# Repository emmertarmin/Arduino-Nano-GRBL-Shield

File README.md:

# Arduino-Nano-GRBL-Shield
This CNC Shield was designed to replace a "Stepper Bricklet" from Tinkerforge. It is much larger in size, but the four screw holes are compatible in size and placement.

## Features
- 102mm x 50mm
- Arduino Nano pinout is designed for GRBL firmware.
- 3 individual "X-Y-Z" stepper drivers, with a fourth "A" Axis whose `step` and `dir` pins can be coupled with either of the other three axes.
- Limit switches per axis are connected in series for NC switch operation. This means the Arduino is going to expect a closed circuit on all 6 switches (if switches are enabled in the firmware) and interpret an open circuit as a triggered switch.
- Switches have RC circuits as is [recommended by GRBL](https://github.com/gnea/grbl/wiki/Wiring-Limit-Switches) for noise filtering. These SMD parts can be left unpopulated.
- 12V Barrel Jack power source for stepper motors.
- If Arduino is to be driven without an active USB connection, the 12V source is to be stepped down to 6-7 Volts with a switching regulator. I used [this DSN-1504 one](https://www.hestore.hu/prod_10038118.html?lang=en) from Hestore.
- The only smd parts that are needed for operation are one 10k pullup resistor on the `EN` pin under the Arduino, and 12 pieces of 100k pulldown resistors right next to the stepper drivers, which control `MS1-MS3` pins to set microstepping.

> Please make sure your Arduino Nano can handle an external 6-7V source on VIN and an active USB connection simultaneously. Officially it should be able to do that, but there's stories on the internet about versions of Nanos that got burnt.

> Also, while a direct 12V source on the VIN of the Arduino is officially fine, it's not recommended, as the internal regulator of the Arduino will dissipate the 7V difference in form of heat. This is why I used a switching step-down converter.

## Images

Renders were created with [tracespace.io](https://tracespace.io/)

The images below show an earlier version which lacked the RC filters. Apart from that it's the same. Please excuse the dusty Nano.

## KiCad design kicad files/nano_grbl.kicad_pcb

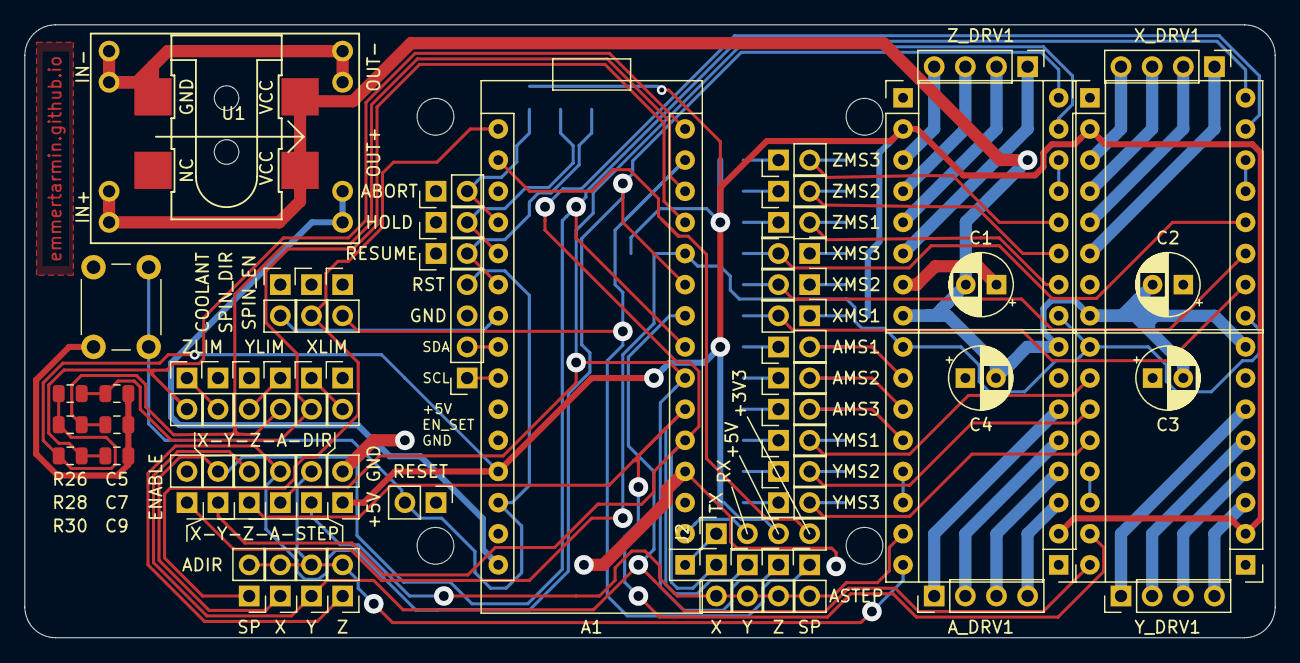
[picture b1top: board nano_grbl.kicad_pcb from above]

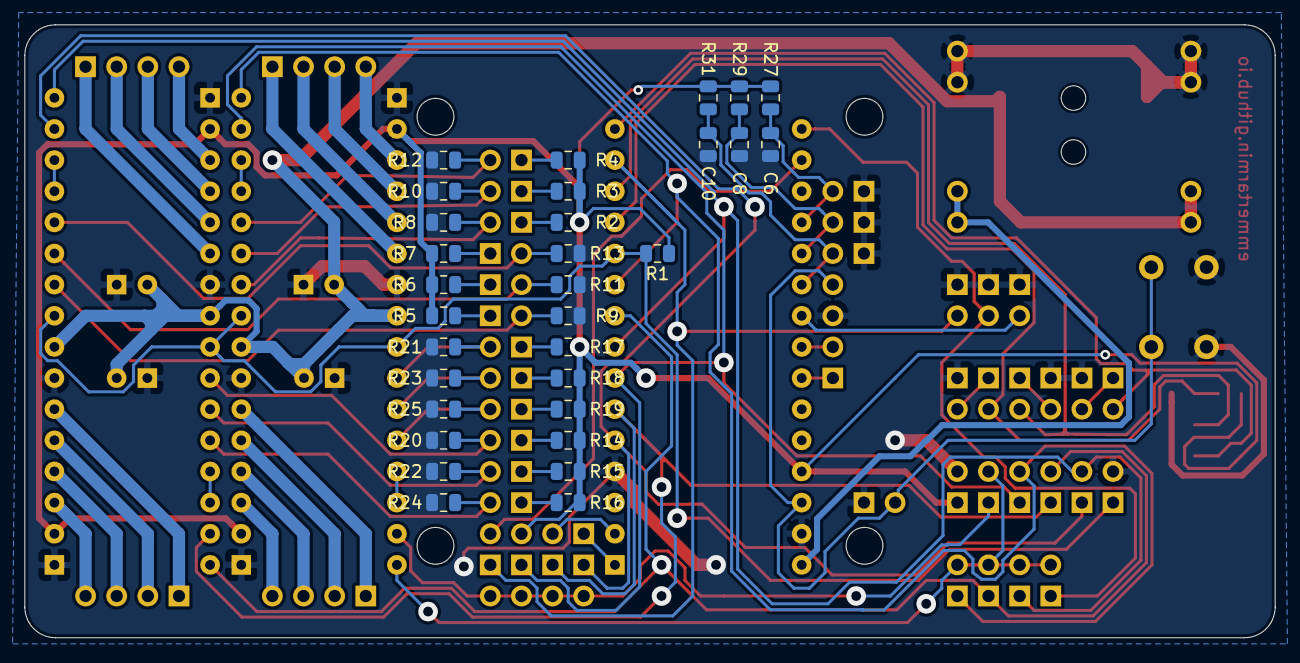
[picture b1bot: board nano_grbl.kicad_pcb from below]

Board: 2 copper layers, 102.0 x 50.0 mm, 94 parts (31 on the bottom side), 75 nets.

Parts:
A1: Arduino_Nano_v3.x; Arduino_Nano
A_DRV1: A_DRV; Pololu_Breakout-16_15.2x20.3mm
C1, C2, C3, C4: 100uF; CP_Radial_D5.0mm_P2.50mm
C5, C6, C7, C8, C9, C10: 100nF; C_0805_2012Metric
J1: Barrel_Jack; Barrel_Jack_2.1x5.5_Custom_SMT
J2: UART; PinSocket_1x04_P2.54mm_Vertical
J3: I2C; PinSocket_1x04_P2.54mm_Vertical
J5: ZMOT; PinHeader_1x04_P2.54mm_Vertical
J6: XMOT; PinHeader_1x04_P2.54mm_Vertical
J7: YMOT; PinHeader_1x04_P2.54mm_Vertical
J8: AMOT; PinHeader_1x04_P2.54mm_Vertical
JP1: ESTOP; PinHeader_1x02_P2.54mm_Vertical
JP2, JP3, JP4, JP5, JP6, JP7, JP8, JP9, JP10, JP11, JP12, JP13, JP14, JP15, JP16, JP17, JP18, JP19, JP20, JP21, JP22, JP23, JP24, JP25, JP26, JP27, JP28, JP29, JP30, JP31, JP32, JP33, JP34, JP35, JP36, JP37, JP38, JP39: Jumper_NO_Small; PinHeader_1x02_P2.54mm_Vertical
R1, R2, R3, R4, R5, R6, R7, R14, R15, R16, R17, R18, R19, R26, R27, R28, R29, R30, R31: 10K; R_0805_2012Metric
R8, R9, R10, R11, R12, R13, R20, R21, R22, R23, R24, R25: 100K; R_0805_2012Metric
SW1: SW_Push; SW_PUSH_6mm
U1: buck_conv
X_DRV1: X_DRV; Pololu_Breakout-16_15.2x20.3mm
Y_DRV1: Y_DRV; Pololu_Breakout-16_15.2x20.3mm
Z_DRV1: Z_DRV; Pololu_Breakout-16_15.2x20.3mm

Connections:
+3V3: A1.17, J2.4
+5V: A1.27, A_DRV1.2, J2.3, JP11.1, R1.1, R2.2, R3.2, R4.2, R5.2, R6.2, R7.2, R14.2, R15.2, R16.2, R17.2, R18.2, R19.2, R26.1, R27.1, R28.1, R29.1, R30.1, R31.1, X_DRV1.2, Y_DRV1.2, Z_DRV1.2
+12V: A_DRV1.8, C1.2, C2.2, C3.2, C4.2, J1.1, U1.1, X_DRV1.8, Y_DRV1.8, Z_DRV1.8
ABORT: A1.19, C6.2, JP25.2, R27.2
ADIR: A_DRV1.16, JP10.2, JP12.2, JP13.2, JP14.2, JP15.2
ASTEP: A_DRV1.15, JP2.2, JP3.2, JP4.2, JP5.2, JP10.1
COOLANT: A1.22, JP24.2
EN: A1.11, A_DRV1.9, JP6.1, R1.2, X_DRV1.9, Y_DRV1.9, Z_DRV1.9
GND: A1.4, A1.29, A_DRV1.1, A_DRV1.7, C1.1, C2.1, C3.1, C4.1, C5.1, C6.1, C7.1, C8.1, C9.1, C10.1, J1.2, J3.3, JP1.1, JP6.2, JP11.2, JP17.1, JP19.1, JP21.1, JP22.1, JP23.1, JP24.1, JP25.1, JP26.1, JP27.1, R8.2, R9.2, R10.2, R11.2, R12.2, R13.2, R20.2, R21.2, R22.2, R23.2, R24.2, R25.2, SW1.1, U1.2, U1.4, X_DRV1.1, X_DRV1.7, Y_DRV1.1, Y_DRV1.7, Z_DRV1.1, Z_DRV1.7
HOLD: A1.20, C8.2, JP26.2, R29.2
unnamed: A1.30, U1.3
unnamed: A_DRV1.3, J8.4
unnamed: A_DRV1.4, J8.3
unnamed: A_DRV1.5, J8.2
unnamed: A_DRV1.6, J8.1
unnamed: A_DRV1.10, JP37.2, R21.1
unnamed: A_DRV1.11, JP38.2, R23.1
unnamed: A_DRV1.12, JP39.2, R25.1
unnamed: A_DRV1.13, A_DRV1.14
unnamed: J5.1, Z_DRV1.6
unnamed: J5.2, Z_DRV1.5
unnamed: J5.3, Z_DRV1.4
unnamed: J5.4, Z_DRV1.3
unnamed: J6.1, X_DRV1.6
unnamed: J6.2, X_DRV1.5
unnamed: J6.3, X_DRV1.4
unnamed: J6.4, X_DRV1.3
unnamed: J7.1, Y_DRV1.6
unnamed: J7.2, Y_DRV1.5
unnamed: J7.3, Y_DRV1.4
unnamed: J7.4, Y_DRV1.3
unnamed: JP16.1, JP17.2
unnamed: JP18.1, JP19.2
unnamed: JP20.1, JP21.2
unnamed: JP28.1, R2.1
unnamed: JP28.2, R8.1, Z_DRV1.10
unnamed: JP29.1, R3.1
unnamed: JP29.2, R10.1, Z_DRV1.11
unnamed: JP30.1, R4.1
unnamed: JP30.2, R12.1, Z_DRV1.12
unnamed: JP31.1, R5.1
unnamed: JP31.2, R9.1, X_DRV1.10
unnamed: JP32.1, R6.1
unnamed: JP32.2, R11.1, X_DRV1.11
unnamed: JP33.1, R7.1
unnamed: JP33.2, R13.1, X_DRV1.12
unnamed: JP34.1, R14.1
unnamed: JP34.2, R20.1, Y_DRV1.10
unnamed: JP35.1, R15.1
unnamed: JP35.2, R22.1, Y_DRV1.11
unnamed: JP36.1, R16.1
unnamed: JP36.2, R24.1, Y_DRV1.12
unnamed: JP37.1, R17.1
unnamed: JP38.1, R18.1
unnamed: JP39.1, R19.1
unnamed: X_DRV1.13, X_DRV1.14
unnamed: Y_DRV1.13, Y_DRV1.14
unnamed: Z_DRV1.13, Z_DRV1.14
RESET: A1.3, A1.28, J3.4, JP1.2, SW1.2
RESUME: A1.21, C10.2, JP27.2, R31.2
RX: A1.2, J2.2
SCL: A1.24, J3.1
SDA: A1.23, J3.2
SPIN_DIR: A1.16, JP15.1, JP23.2
SPIN_EN: A1.14, JP5.1, JP22.2
TX: A1.1, J2.1
XDIR: A1.8, JP7.2, JP12.1, X_DRV1.16
XLIMIT: A1.12, C5.2, JP20.2, R26.2
XSTEP: A1.5, JP2.1, JP7.1, X_DRV1.15
YDIR: A1.9, JP8.2, JP13.1, Y_DRV1.16
YLIMIT: A1.13, C7.2, JP18.2, R28.2
YSTEP: A1.6, JP3.1, JP8.1, Y_DRV1.15
ZDIR: A1.10, JP9.2, JP14.1, Z_DRV1.16
ZLIMIT: A1.15, C9.2, JP16.2, R30.2
ZSTEP: A1.7, JP4.1, JP9.1, Z_DRV1.15

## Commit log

2020-07-20 extended README
2020-07-22 corrected RxTx silkscreen
